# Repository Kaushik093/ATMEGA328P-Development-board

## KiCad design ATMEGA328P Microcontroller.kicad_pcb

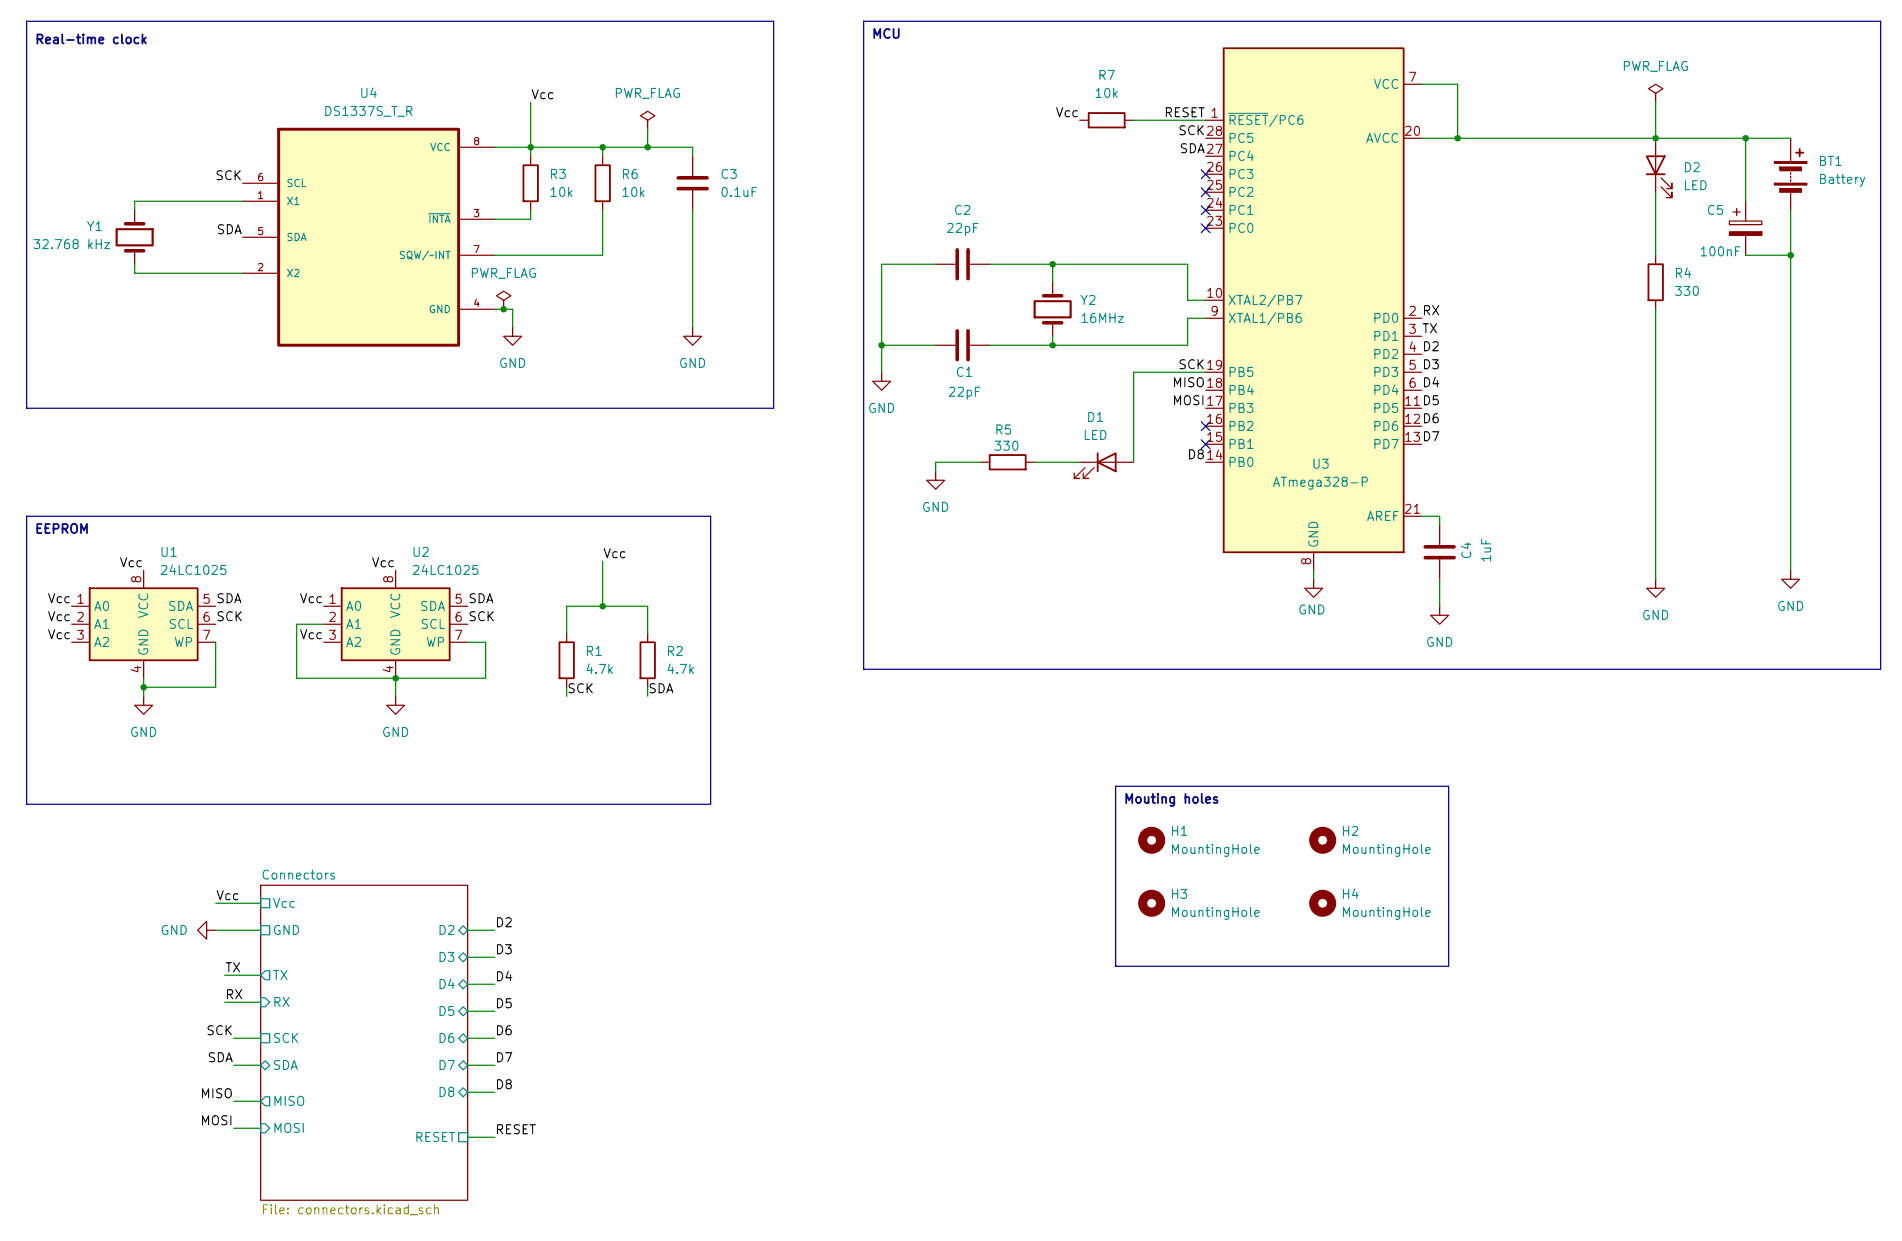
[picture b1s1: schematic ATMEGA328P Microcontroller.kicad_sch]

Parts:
BT1: Battery; PinHeader_1x02_P2.54mm_Vertical
C1, C2: 22pF; C_0805_2012Metric
C3: 0.1uF; C_0805_2012Metric
C4: 1uF; C_0805_2012Metric
C5: 100nF; C_0805_2012Metric
D1, D2: LED; LED_0805_2012Metric
H1, H2, H3, H4: MountingHole; MountingHole_2.2mm_M2
R1, R2: 4.7k; R_0805_2012Metric
R3, R6, R7: 10k; R_0805_2012Metric
R4, R5: 330; R_0805_2012Metric
U1, U2: 24LC1025; SOIC-8_5.23x5.23mm_P1.27mm
U3: ATmega328-P; DIP-28_W7.62mm
U4: DS1337S_T_R; SOIC127P600X175-8N
Y1: 32.768 kHz; Crystal_SMD_0603-2Pin_6.0x3.5mm_HandSoldering
Y2: 16MHz; Crystal_SMD_0603-2Pin_6.0x3.5mm_HandSoldering

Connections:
/D2: U3.4 (PD2); also elsewhere on the board
/D3: U3.5 (PD3); also elsewhere on the board
/D4: U3.6 (PD4); also elsewhere on the board
/D5: U3.11 (PD5); also elsewhere on the board
/D6: U3.12 (PD6); also elsewhere on the board
/D7: U3.13 (PD7); also elsewhere on the board
/D8: U3.14 (PB0); also elsewhere on the board
/MISO: U3.18 (PB4); also elsewhere on the board
/MOSI: U3.17 (PB3); also elsewhere on the board
/RESET: R7.2, U3.1 (~RESET/PC6); also elsewhere on the board
/RX: U3.2 (PD0); also elsewhere on the board
/SCK: D1.2 (A), R1.2, U1.6 (SCL), U2.6 (SCL), U3.19 (PB5), U3.28 (PC5), U4.6 (SCL); also elsewhere on the board
/SDA: R2.2, U1.5 (SDA), U2.5 (SDA), U3.27 (PC4), U4.5 (SDA); also elsewhere on the board
/TX: U3.3 (PD1); also elsewhere on the board
/Vcc: C3.1, R1.1, R2.1, R3.1, R6.1, R7.1, U1.1 (A0), U1.2 (A1), U1.3 (A2), U1.8 (VCC), U2.1 (A0), U2.3 (A2), U2.8 (VCC), U4.8 (VCC); also elsewhere on the board
GND: BT1.2 (-), C1.1, C2.1, C3.2, C4.1, C5.2, R4.2, R5.1, U1.4 (GND), U1.7 (WP), U2.2 (A1), U2.4 (GND), U2.7 (WP), U3.8 (GND), U3.22 (GND), U4.4 (GND); also elsewhere on the board
unnamed: BT1.1 (+), C5.1, D2.2 (A), U3.7 (VCC), U3.20 (AVCC)
unnamed: D1.1 (K), R5.2
unnamed: D2.1 (K), R4.1
unnamed: C4.2, U3.21 (AREF)
unnamed: C1.2, U3.9 (XTAL1/PB6), Y2.1
unnamed: C2.2, U3.10 (XTAL2/PB7), Y2.2
unnamed: R6.2, U4.7 (SQW/~INT)
unnamed: U4.1 (X1), Y1.1
unnamed: U4.2 (X2), Y1.2
unnamed: R3.2, U4.3 (~INTA)

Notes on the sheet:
Mouting holes
MCU
EEPROM
Real-time clock

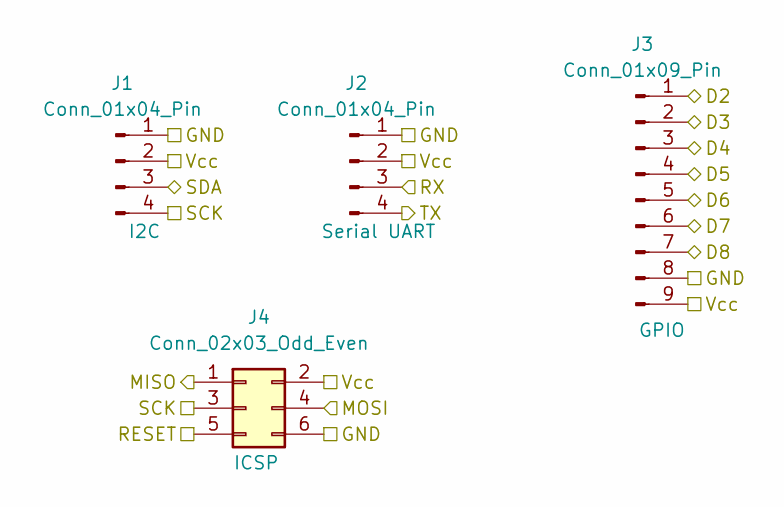
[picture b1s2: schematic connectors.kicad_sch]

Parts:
J1, J2: Conn_01x04_Pin; PinHeader_1x04_P2.54mm_Vertical
J3: Conn_01x09_Pin; PinHeader_1x09_P2.54mm_Vertical
J4: Conn_02x03_Odd_Even; PinHeader_2x03_P2.54mm_Vertical

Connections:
/D2: J3.1; also elsewhere on the board
/D3: J3.2; also elsewhere on the board
/D4: J3.3; also elsewhere on the board
/D5: J3.4; also elsewhere on the board
/D6: J3.5; also elsewhere on the board
/D7: J3.6; also elsewhere on the board
/D8: J3.7; also elsewhere on the board
/MISO: J4.1; also elsewhere on the board
/MOSI: J4.4; also elsewhere on the board
/RESET: J4.5; also elsewhere on the board
/RX: J2.3; also elsewhere on the board
/SCK: J1.4, J4.3; also elsewhere on the board
/SDA: J1.3; also elsewhere on the board
/TX: J2.4; also elsewhere on the board
/Vcc: J1.2, J2.2, J3.9, J4.2; also elsewhere on the board
GND: J1.1, J2.1, J3.8, J4.6; also elsewhere on the board

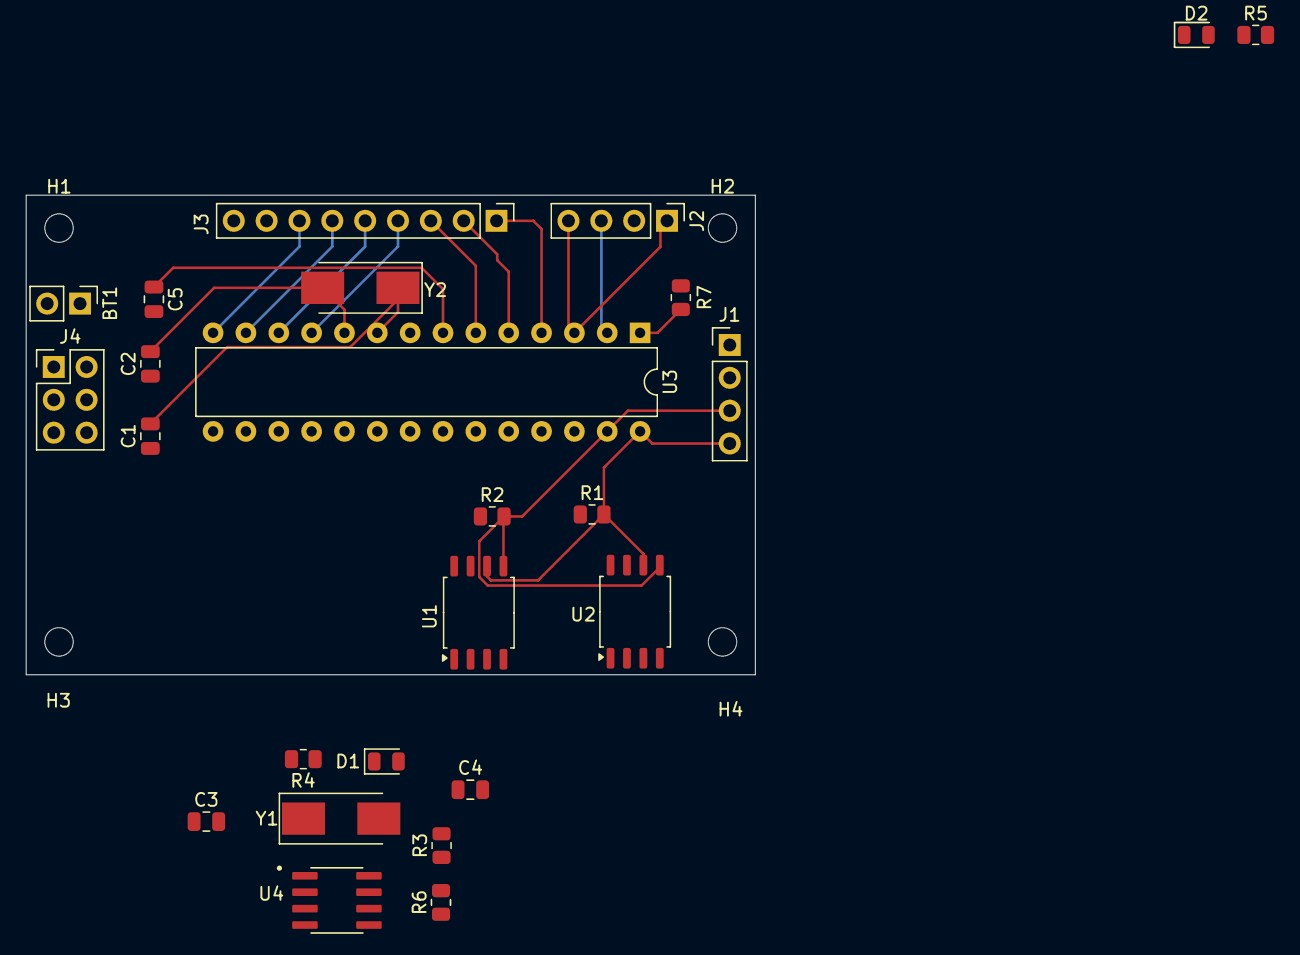
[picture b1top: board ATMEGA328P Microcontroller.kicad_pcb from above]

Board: 2 copper layers, 56.4 x 37.1 mm, 29 parts (0 on the bottom side), 26 nets.

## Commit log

2024-06-21 Add .gitignore
2024-06-23 Added symbols to schematic
2024-06-23 Arranged symbols in schematic
2024-06-23 Added values to components
2024-06-23 Associated footprints
2024-06-24 Wiring complete
2024-06-24 Allocated Vcc and GND nets to Power netclass
2024-06-24 Added comments to schematic
2024-06-24 Placed footprints on layout
2024-06-26 Updated block diagram and layout in progress
2024-08-11 Layout complete
2024-08-11 3D models updated
2024-08-11 Added silkscreen
